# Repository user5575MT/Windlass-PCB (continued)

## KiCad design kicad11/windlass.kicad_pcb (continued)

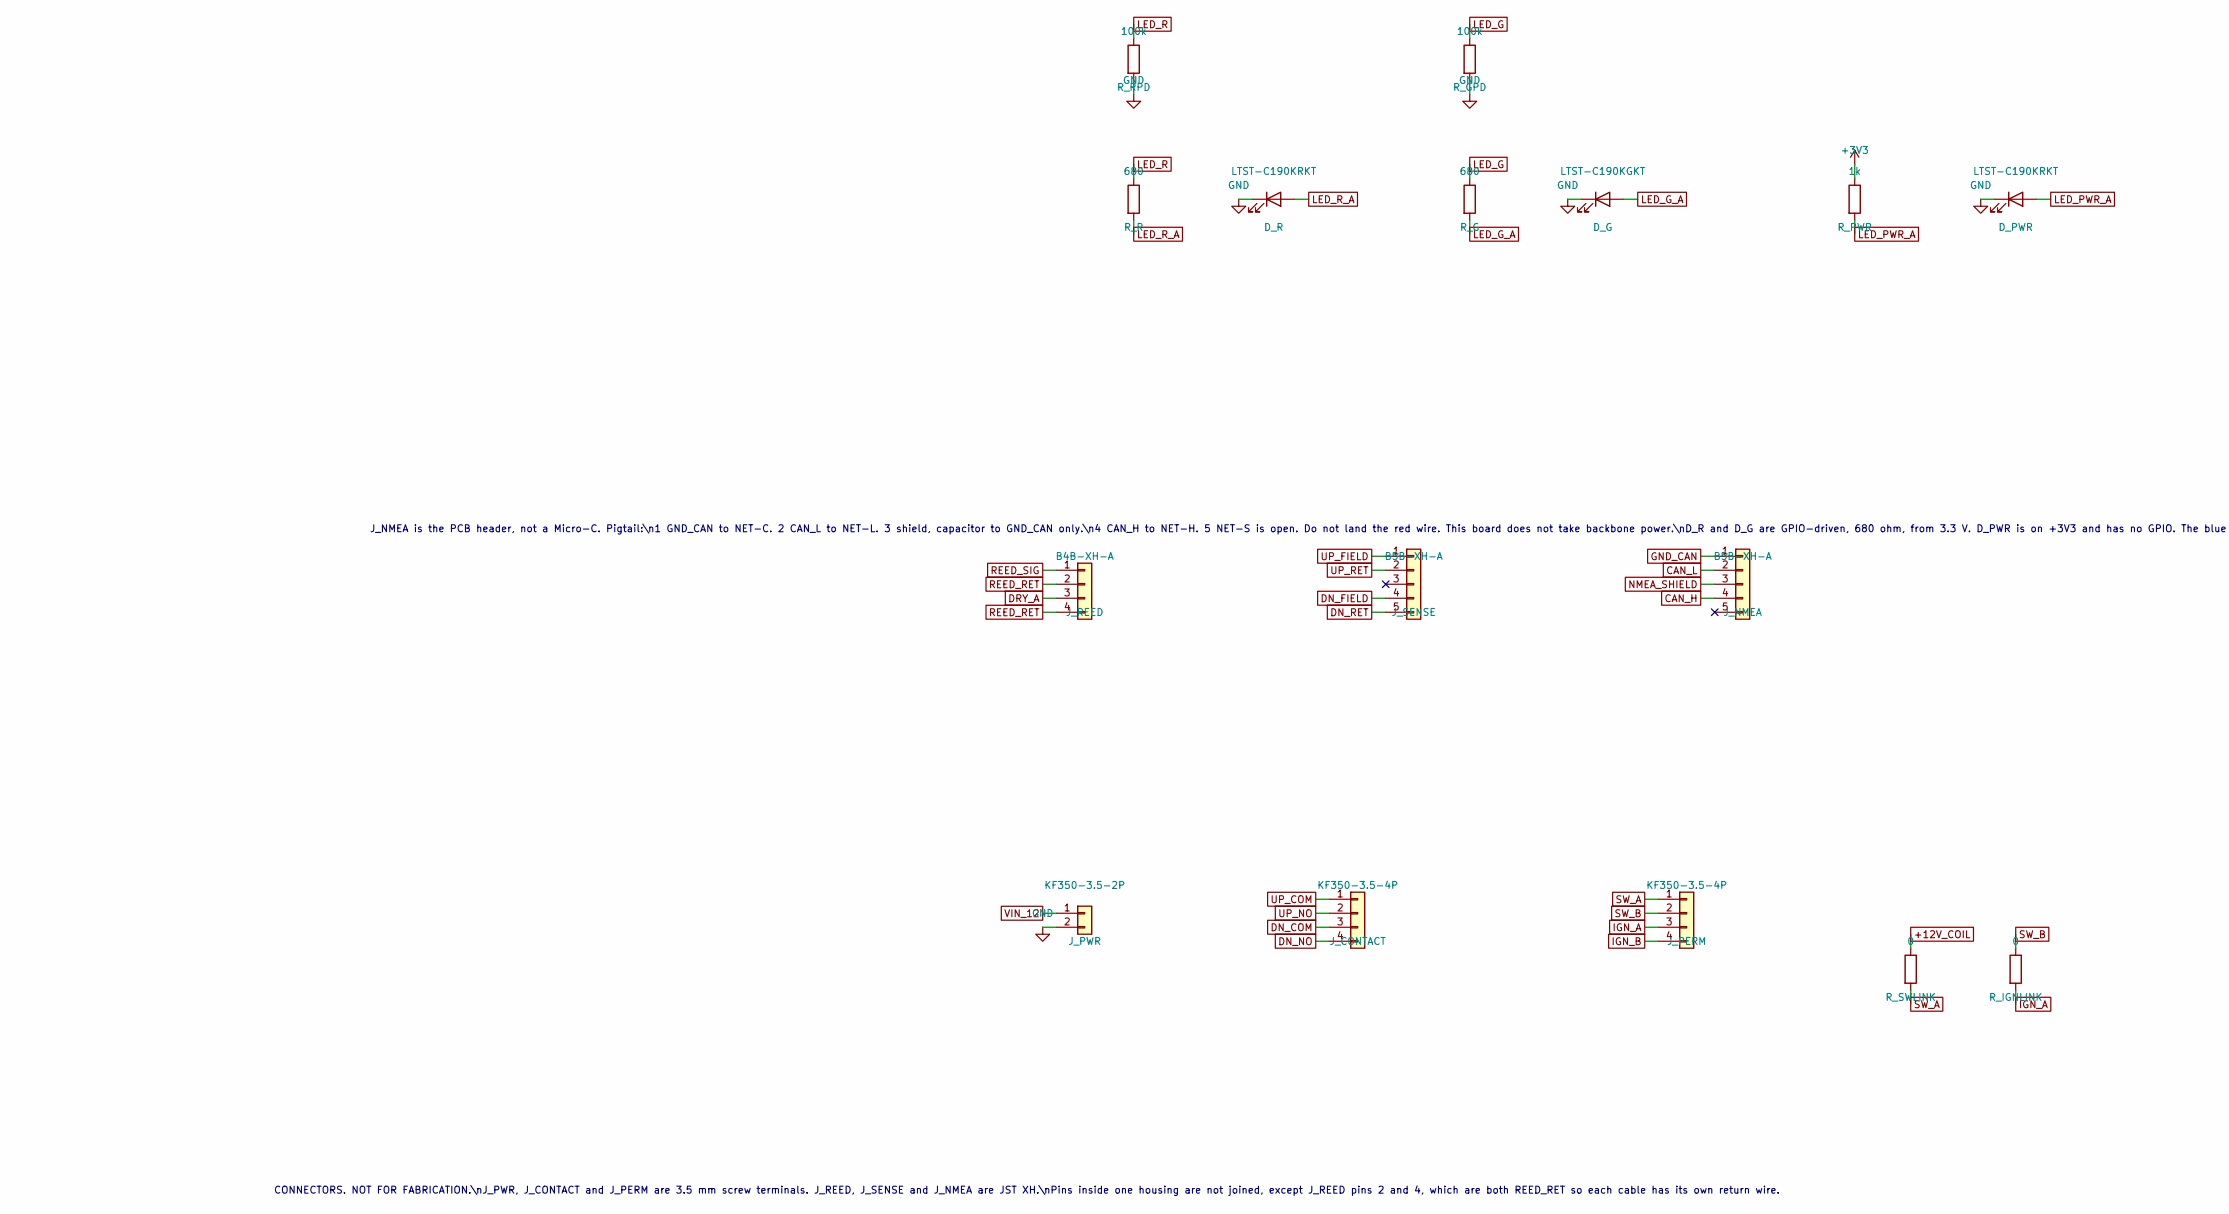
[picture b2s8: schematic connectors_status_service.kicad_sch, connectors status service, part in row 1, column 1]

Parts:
D_G: LTST-C190KGKT; LED_0603_1608Metric
D_PWR: LTST-C190KRKT; LED_0603_1608Metric
D_R: LTST-C190KRKT; LED_0603_1608Metric
J_CONTACT: KF350-3.5-4P; KF350-3.5-1x04
J_NMEA: B5B-XH-A; JST_XH_B5B-XH-A_1x05_P2.50mm_Vertical
J_PERM: KF350-3.5-4P; KF350-3.5-1x04
J_PWR: KF350-3.5-2P; KF350-3.5-1x02
J_REED: B4B-XH-A; JST_XH_B4B-XH-A_1x04_P2.50mm_Vertical
J_SENSE: B5B-XH-A; JST_XH_B5B-XH-A_1x05_P2.50mm_Vertical
R_G: 680; R_0402_1005Metric
R_GPD: 100k; R_0402_1005Metric
R_IGNLINK: 0; R_0402_1005Metric
R_PWR: 1k; R_0402_1005Metric
R_R: 680; R_0402_1005Metric
R_RPD: 100k; R_0402_1005Metric
R_SWLINK: 0; R_0402_1005Metric

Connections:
+3V3: R_PWR.1; also elsewhere on the board
+12V_COIL: R_SWLINK.1; also elsewhere on the board
CAN_H: J_NMEA.4; also elsewhere on the board
CAN_L: J_NMEA.2; also elsewhere on the board
DN_COM: J_CONTACT.3; also elsewhere on the board
DN_FIELD: J_SENSE.4; also elsewhere on the board
DN_NO: J_CONTACT.4; also elsewhere on the board
DN_RET: J_SENSE.5; also elsewhere on the board
DRY_A: J_REED.3; also elsewhere on the board
GND: D_G.1 (K), D_PWR.1 (K), D_R.1 (K), J_PWR.2, R_GPD.2, R_RPD.2; also elsewhere on the board
GND_CAN: J_NMEA.1; also elsewhere on the board
IGN_A: J_PERM.3, R_IGNLINK.2
IGN_B: J_PERM.4; also elsewhere on the board
LED_G: R_G.1, R_GPD.1; also elsewhere on the board
LED_G_A: D_G.2 (A), R_G.2
LED_PWR_A: D_PWR.2 (A), R_PWR.2
LED_R: R_R.1, R_RPD.1; also elsewhere on the board
LED_R_A: D_R.2 (A), R_R.2
NMEA_SHIELD: J_NMEA.3; also elsewhere on the board
REED_RET: J_REED.2, J_REED.4; also elsewhere on the board
REED_SIG: J_REED.1; also elsewhere on the board
SW_A: J_PERM.1, R_SWLINK.2
SW_B: J_PERM.2, R_IGNLINK.1
UP_COM: J_CONTACT.1; also elsewhere on the board
UP_FIELD: J_SENSE.1; also elsewhere on the board
UP_NO: J_CONTACT.2; also elsewhere on the board
UP_RET: J_SENSE.2; also elsewhere on the board
VIN_12: J_PWR.1; also elsewhere on the board

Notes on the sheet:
CONNECTORS. NOT FOR FABRICATION.\nJ_PWR, J_CONTACT and J_PERM are 3.5 mm screw terminals. J_REED, J_SENSE and J_NMEA are JST XH.\nPins inside one housing are not joined, except J_REED pins 2 and 4, which are both REED_RET so each cable has its own return wire.
J_NMEA is the PCB header, not a Micro-C. Pigtail:\n1 GND_CAN to NET-C. 2 CAN_L to NET-L. 3 shield, capacitor to GND_CAN only.\n4 CAN_H to NET-H. 5 NET-S is open. Do not land the red wire. This board does not take backbone power.\nD_R and D_G are GPIO-driven, 680 ohm, from 3.3 V. D_PWR is on +3V3 an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

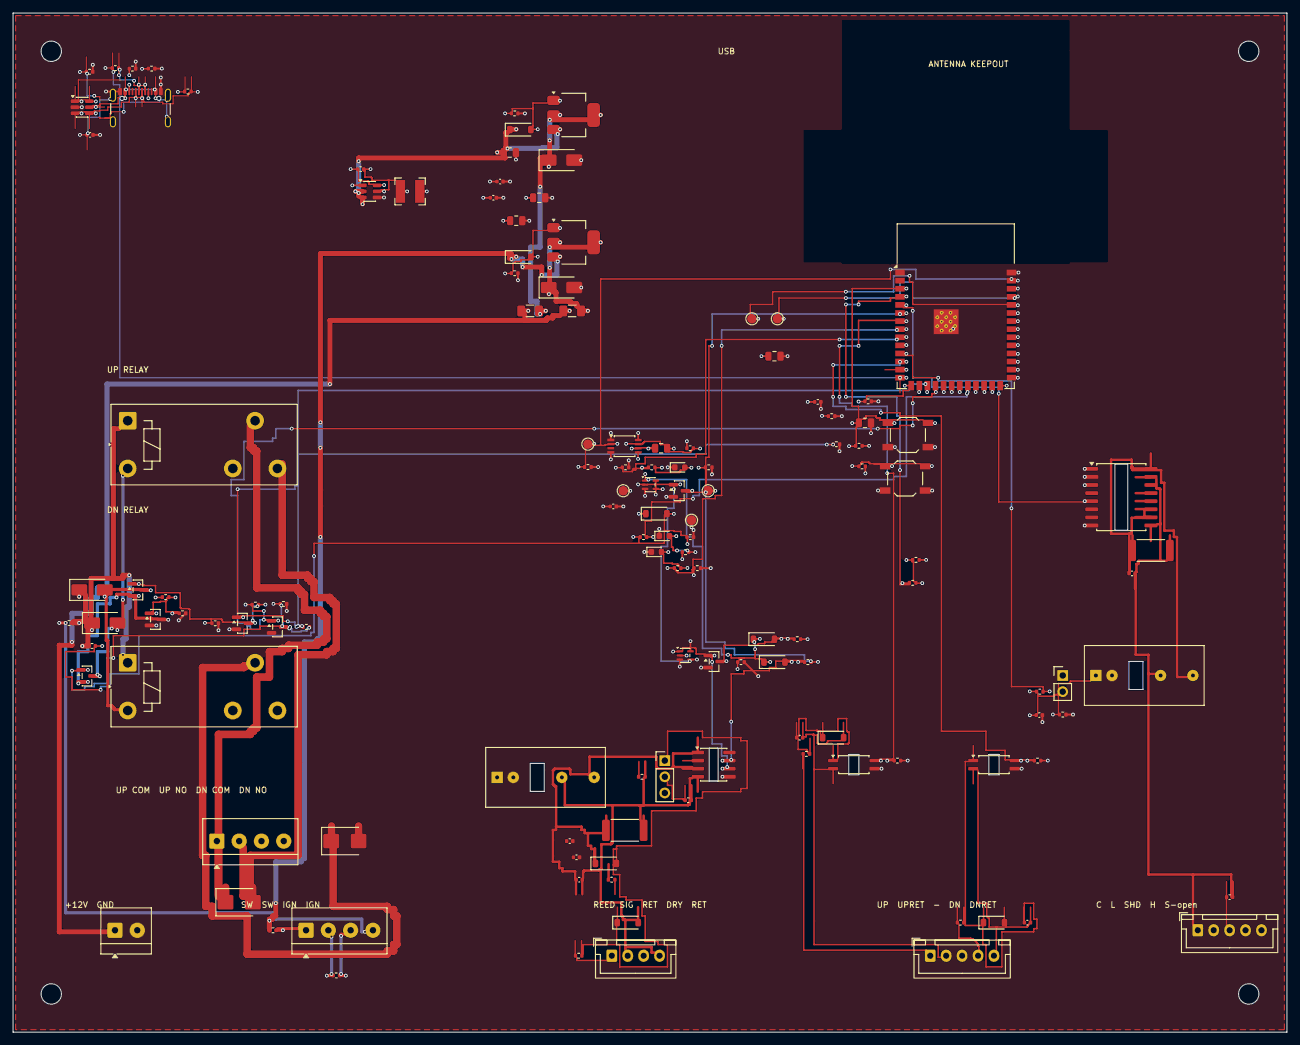
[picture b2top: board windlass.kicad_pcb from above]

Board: 4 copper layers, 200.0 x 160.0 mm, 134 parts (0 on the bottom side), 83 nets.

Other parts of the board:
H1, H2, H3, H4: M3; MountingHole_3.2mm_M3

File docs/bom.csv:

"Reference","Value","Footprint"
"C10","1uF","Capacitor_SMD:C_0805_2012Metric"
"C11","10uF","Capacitor_SMD:C_0805_2012Metric"
"C12","100nF","Capacitor_SMD:C_0402_1005Metric"
"C13","100nF","Capacitor_SMD:C_0402_1005Metric"
"C20","100nF","Capacitor_SMD:C_0402_1005Metric"
"C21","100nF","Capacitor_SMD:C_0402_1005Metric"
"C22","1nF","Capacitor_SMD:C_0402_1005Metric"
"C24","100nF","Capacitor_SMD:C_0402_1005Metric"
"C30","100nF","Capacitor_SMD:C_0402_1005Metric"
"C30A?","22uF","Capacitor_SMD:C_0805_2012Metric"
"C30B?","100nF","Capacitor_SMD:C_0402_1005Metric"
"C30C?","22uF","Capacitor_SMD:C_0805_2012Metric"
"C30I?","10uF","Capacitor_SMD:C_0805_2012Metric"
"C40","100nF","Capacitor_SMD:C_0402_1005Metric"
"C40A?","22uF","Capacitor_SMD:C_0805_2012Metric"
"C40B?","100nF","Capacitor_SMD:C_0402_1005Metric"
"C40C?","22uF","Capacitor_SMD:C_0805_2012Metric"
"C40I?","10uF","Capacitor_SMD:C_0805_2012Metric"
"C50","3.3uF","Capacitor_SMD:C_0805_2012Metric"
"C51","100nF","Capacitor_SMD:C_0402_1005Metric"
"C90","100nF","Capacitor_SMD:C_0402_1005Metric"
"C91","100nF","Capacitor_SMD:C_0402_1005Metric"
"C92","100nF","Capacitor_SMD:C_0402_1005Metric"
"C93","100nF","Capacitor_SMD:C_0402_1005Metric"
"D20","BAT54W","Diode_SMD:D_SOD-123"
"D21","BAT54W","Diode_SMD:D_SOD-123"
"D30","1N4148W_ANTIPARALLEL","Diode_SMD:D_SOD-123"
"D40","1N4148W_ANTIPARALLEL","Diode_SMD:D_SOD-123"
"D60","SS14","Diode_SMD:D_SMA"
"D70","SS14","Diode_SMD:D_SMA"
"D80","SCHOTTKY_CLAMP","Diode_SMD:D_SOD-123"
"D_B?","LTST-C190TBKT","LED_SMD:LED_0603_1608Metric"
"D_G?","LTST-C190KGKT","LED_SMD:LED_0603_1608Metric"
"D_R?","LTST-C190KRKT","LED_SMD:LED_0603_1608Metric"
"D_TVS_COIL?","SMAJ18A","Diode_SMD:D_SMA"
"D_TVS_MCU?","SMAJ18A","Diode_SMD:D_SMA"
"D_Z_COIL?","BZT52C12","Diode_SMD:D_SOD-123"
"D_Z_MCU?","BZT52C12","Diode_SMD:D_SOD-123"
"F_5V?","2A_antisurge","Fuse:Fuse_1206_3216Metric"
"F_COIL?","1A_0466001","Fuse:Fuse_1206_3216Metric"
"F_MCU?","2A_0466002","Fuse:Fuse_1206_3216Metric"
"JP1","Jumper_2_Open","Connector_PinHeader_2.54mm:PinHeader_1x02_P2.54mm_Vertical"
"JP_REED?","HDR_1x03_2.54","Connector_PinHeader_2.54mm:PinHeader_1x03_P2.54mm_Vertical"
"J_CONTACT?","KF350-3.5-4P","windlass:KF350-3.5-1x04"
"J_NMEA?","B5B-XH-A(LF)(SN)","Connector_JST:JST_XH_B5B-XH-A_1x05_P2.50mm_Vertical"
"J_PERM?","KF350-3.5-4P","windlass:KF350-3.5-1x04"
"J_PWR?","KF350-3.5-2P","windlass:KF350-3.5-1x02"
"J_REED?","B4B-XH-A(LF)(SN)","Connector_JST:JST_XH_B4B-XH-A_1x04_P2.50mm_Vertical"
"J_SENSE?","B5B-XH-A(LF)(SN)","Connector_JST:JST_XH_B5B-XH-A_1x05_P2.50mm_Vertical"
"J_USB?","TYPE-C-31-M-12","Connector_USB:USB_C_Receptacle_HRO_TYPE-C-31-M-12"
"K_DN?","40.31.7.012.0000","Relay_THT:Relay_SPDT_Finder_40.31"
"K_UP?","40.31.7.012.0000","Relay_THT:Relay_SPDT_Finder_40.31"
"L20","3.9uH","Inductor_SMD:L_Bourns-SRN4018"
"L21","4.7uH","Inductor_SMD:L_Bourns-SRN4018"
"Q90","2N7002","Package_TO_SOT_SMD:SOT-23"
"Q91","DMP3099L","Package_TO_SOT_SMD:SOT-23"
"Q_CLAMP_DN?","2N7002","Package_TO_SOT_SMD:SOT-23"
"Q_CLAMP_UP?","2N7002","Package_TO_SOT_SMD:SOT-23"
"Q_COIL?","DMP6023LE-13","Package_TO_SOT_SMD:SOT-223-3_TabPin2"
"Q_DN?","NX6008NBK","Package_TO_SOT_SMD:SOT-23"
"Q_LED?","2N7002BK,215","Package_TO_SOT_SMD:SOT-23"
"Q_MCU?","DMP6023LE-13","Package_TO_SOT_SMD:SOT-223-3_TabPin2"
"Q_SERIES?","NX6008NBK","Package_TO_SOT_SMD:SOT-23"
"Q_UP?","NX6008NBK","Package_TO_SOT_SMD:SOT-23"
"R10","10k","Resistor_SMD:R_0402_1005Metric"
"R11","10k","Resistor_SMD:R_0402_1005Metric"
"R12","10k","Resistor_SMD:R_0402_1005Metric"
"R13","100k","Resistor_SMD:R_0402_1005Metric"
"R14","100k","Resistor_SMD:R_0402_1005Metric"
"R15","5.1k","Resistor_SMD:R_0402_1005Metric"
"R16","5.1k","Resistor_SMD:R_0402_1005Metric"
"R17","22","Resistor_SMD:R_0402_1005Metric"
"R18","22","Resistor_SMD:R_0402_1005Metric"
"R19","1M","Resistor_SMD:R_0402_1005Metric"
"R20","10k","Resistor_SMD:R_0402_1005Metric"
"R22","4.7k","Resistor_SMD:R_0402_1005Metric"
"R23","47k","Resistor_SMD:R_0402_1005Metric"
"R24","51_0.5W","Resistor_SMD:R_2512_6332Metric"
"R30","R_IN_OPEN","Resistor_SMD:R_0402_1005Metric"
"R30P?","10k","Resistor_SMD:R_0402_1005Metric"
"R40","R_IN_OPEN","Resistor_SMD:R_0402_1005Metric"
"R40P?","10k","Resistor_SMD:R_0402_1005Metric"
"R50","100","Resistor_SMD:R_0402_1005Metric"
"R51","100k","Resistor_SMD:R_0402_1005Metric"
"R52","100k","Resistor_SMD:R_0402_1005Metric"
"R53","100k","Resistor_SMD:R_0402_1005Metric"
"R60","10k","Resistor_SMD:R_0402_1005Metric"
"R61","100k","Resistor_SMD:R_0402_1005Metric"
"R70","10k","Resistor_SMD:R_0402_1005Metric"
"R71","100k","Resistor_SMD:R_0402_1005Metric"
"R80","100k","Resistor_SMD:R_0402_1005Metric"
"R81","100k","Resistor_SMD:R_0402_1005Metric"
"R82","1k","Resistor_SMD:R_0402_1005Metric"
"R90","100k","Resistor_SMD:R_0402_1005Metric"
"R91","100k","Resistor_SMD:R_0402_1005Metric"
"R92","10k","Resistor_SMD:R_0402_1005Metric"
"R93","33","Resistor_SMD:R_0402_1005Metric"
"R94","120_0.5W","Resistor_SMD:R_2512_6332Metric"
"R_B?","1k","Resistor_SMD:R_0402_1005Metric"
"R_BPD?","100k","Resistor_SMD:R_0402_1005Metric"
"R_COILFEED?","0","Resistor_SMD:R_0402_1005Metric"
"R_COIL_G?","100k","Resistor_SMD:R_0402_1005Metric"
"R_G?","680","Resistor_SMD:R_0402_1005Metric"
"R_GPD?","100k","Resistor_SMD:R_0402_1005Metric"
"R_IGNLINK?","0","Resistor_SMD:R_0402_1005Metric"
"R_MCU_G?","100k","Resistor_SMD:R_0402_1005Metric"
"R_R?","680","Resistor_SMD:R_0402_1005Metric"
"R_RPD?","100k","Resistor_SMD:R_0402_1005Metric"
"R_SWLINK?","0","Resistor_SMD:R_0402_1005Metric"
"SH_REED?","SHUNT_2.54",""
"SW_BOOT?","TL3342F160QG","Button_Switch_SMD:SW_SPST_TL3342"
"SW_RST?","TL3342F160QG","Button_Switch_SMD:SW_SPST_TL3342"
"TP_RX?","TESTPAD","TestPoint:TestPoint_Pad_D1.5mm"
"TP_TX?","TESTPAD","TestPoint:TestPoint_Pad_D1.5mm"
"TP_VBUS?","TESTPAD","TestPoint:TestPoint_Pad_D1.5mm"
"TP_WDI?","TESTPAD","TestPoint:TestPoint_Pad_D1.5mm"
"U3","ESP32-S3-WROOM-1-N16","RF_Module:ESP32-S3-WROOM-1"
"U4","MEJ2S0503SC","windlass:Murata_MEJ2SxxxxSC"
"U5","ISO7721DR","Package_SO:SOIC-8_3.9x4.9mm_P1.27mm"
"U6","TLP291(GB-TP,SE","Package_SO:SOIC-4_4.55x2.6mm_P1.27mm"
"U7","TLP291(GB-TP,SE","Package_SO:SOIC-4_4.55x2.6mm_P1.27mm"
"U8","74LVC1G86GW,125","Package_TO_SOT_SMD:SOT-353_SC-70-5"
"U9","MEJ2S0505SC","windlass:Murata_MEJ2SxxxxSC"
"U10","ISO1042BDWR","Package_SO:SOIC-16W_7.5x10.3mm_P1.27mm"
"U11","74LVC1G123DP,125","Package_SO:TSSOP-8_3x3mm_P0.65mm"
"U12","74LVC1G08GW,125","Package_TO_SOT_SMD:SOT-353_SC-70-5"
"U20","AP63203WU","Package_TO_SOT_SMD:TSOT-23-6"
"U21","AP63205WU","Package_TO_SOT_SMD:TSOT-23-6"
"U_ESD?","USBLC6-2SC6","Package_TO_SOT_SMD:SOT-23-6"

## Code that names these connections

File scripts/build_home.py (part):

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    s.flag(120, 560, "CAN_VIN")

    # --- 12 V input, two branches ---
    bs.multi_pin(s, "Connector_Generic:Conn_01x02", "J_PWR", "KF350-3.5-2P", *cell(0, 0), ["VIN_12", "GND"], FP["kf2"])
    bs.two_pin(s, "Device:Fuse", "F_MCU", "0217002.HXP", *cell(0, 1), "VIN_12", "VIN_MCU", FP["fuse"])
    bs.two_pin(s, "Device:D", "D_TVS_MCU", "P6KE18A", *cell(0, 2), "VIN_MCU", "GND", FP["d"])
    q = s.place("Transistor_FET:IRF9540N", "Q_MCU", "IRF9540NPBF", *cell(1, 0), FP["fet"])
    bs.connect_named(s, q, {"D": "VIN_MCU", "S": "+12V_MCU", "G": "QMCU_G"})
    bs.two_pin(s, "Device:R", "R_MCU_G", "100k", *cell(1, 1), "QMCU_G", "GND", FP["r"])
    bs.two_pin(s, "Device:D", "D_Z_MCU", "BZX55C12", *cell(1, 2), "+12V_MCU", "QMCU_G", FP["dz"])
    bs.two_pin(s, "Device:C_Polarized", "C_IN", "10uF_50V", *cell(1, 3), "+12V_MCU", "GND", FP["cp10"])

    bs.two_pin(s, "Device:Fuse", "F_COIL", "0235.250HXP", *cell(0, 3), "VIN_12", "VIN_COIL", FP["fuse"])
    bs.two_pin(s, "Device:D", "D_TVS_COIL", "P6KE18A", *cell(0, 4), "VIN_COIL", "GND", FP["d"])
    q = s.place("Transistor_FET:IRF9540N", "Q_COIL", "IRF9540NPBF", *cell(1, 4), FP["fet"])
    bs.connect_named(s, q, {"D": "VIN_COIL", "S": "+12V_COIL", "G": "QCOIL_G"})
    bs.two_pin(s, "Device:R", "R_COIL_G", "100k", *cell(2, 0), "QCOIL_G", "GND", FP["r"])
    bs.two_pin(s, "Device:D", "D_Z_COIL", "BZX55C12", *cell(2, 1), "+12V_COIL", "QCOIL_G", FP["dz"])

    u = s.place("Converter_DCDC:OKI-78SR-5_1.5-W36H-C", "U20", "OKI-78SR-5/1.5-W36H-C", *cell(2, 2), FP["oki"])
    bs.connect_named(s, u, {"IN": "+12V_MCU", "GND": "GND", "OUT": "+5V"})
    bs.two_pin(s, "Device:C_Polarized", "C_5V", "10uF_25V", *cell(2, 3), "+5V", "GND", FP["cp"])
    bs.two_pin(s, "Device:C", "C_5VHF", "100nF", *cell(2, 4), "+5V", "GND", FP["c"])
    # Anode is pin 2, cathode is pin 1. Current flows from +5V into the DevKit only.
    bs.two_pin(s, "Diode:1N5817", "D_DEV", "1N5817", *cell(3, 0), "DEV_5V", "+5V", FP["d"])
    bs.two_pin(s, "Device:C_Polarized", "C_DEV", "10uF_25V", *cell(3, 1), "DEV_5V", "GND", FP["cp"])

    # --- DevKit sockets. Pin 1 of both headers is the USB end, opposite the antenna. ---
    j1 = {
        "1": "+3V3", "2": "+3V3", "4": "GPIO4", "5": "GPIO5", "6": "GPIO6",
        "7": "GPIO7", "8": "GPIO15", "9": "GPIO16", "11": "GPIO18", "12": "GPIO8",
        "15": "GPIO9", "16": "GPIO10", "20": "GPIO14", "21": "DEV_5V", "22": "GND",
    }
    j3 = {"1": "GND", "4": "GPIO1", "21": "GND", "22": "GND"}
    bs.connect_named(
        s,
        s.place("Connector_Generic:Conn_01x22", "J1", "DevKitC_J1", *cell(0, 6), FP["sock"]),
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        s,
        u,
        {
            "1A": "GPIO1",
            "1Y": "HB_N",
            "2A": "EDGE",
            "2Y": "DISCH",
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            "GND": "GND",
        },
    )
    bs.two_pin(s, "Device:R", "R_HB", "100k", *cell(4, 2), "GPIO1", "GND", FP["r"])
    bs.two_pin(s, "Device:R", "R_EDGE", "330", *cell(4, 3), "HB_N", "EDGE_R", FP["r"])
    bs.two_pin(s, "Device:C", "C_EDGE", "220nF", *cell(5, 0), "EDGE_R", "EDGE", FP["c"])
    bs.two_pin(s, "Device:R", "R_EDGE_PU", "10k", *cell(5, 1), "EDGE", "+5V", FP["r"])
    bs.two_pin(s, "Device:R", "R_BASE", "1k", *cell(5, 2), "DISCH", "DISCH_B", FP["r"])
    q = s.place("Transistor_BJT:BC547", "Q_DIS", "BC547B", *cell(5, 3), FP["q"])
    bs.connect_named(s, q, {"B": "DISCH_B", "C": "TIME", "E": "GND"})
    bs.two_pin(s, "Device:R", "R_TIME", "470k", *cell(5, 4), "+5V", "TIME", FP["r"])
    bs.two_pin(s, "Device:C", "C_TIME", "2.2uF", *cell(6, 0), "TIME", "GND", FP["cfilm"])
    bs.two_pin(s, "Device:C", "C_U12", "100nF", *cell(6, 1), "+5V", "GND", FP["c"])
    bs.two_pin(s, "Device:R", "R50", "470", *cell(6, 2), "WDI_Q", "WDI_GATE", FP["r"])
    bs.two_pin(s, "Device:R", "R_SER_PD", "100k", *cell(6, 3), "WDI_GATE", "GND", FP["r"])

    # --- Request buffers and coil FETs ---
    u = s.place("windlass:CD74HCT125E", "U15", "CD74HCT125E", *cell(7, 0), FP["dip14"])
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        u,
        {
            "1OE": "GND",
            "1A": "GPIO9",
            "1Y": "UP_DRV",
            "2OE": "GND",
            "2A": "GPIO10",
            "2Y": "DN_DRV",
            "3OE": "+5V",
            "3A": "GND",
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        },
    )
    bs.two_pin(s, "Device:C", "C_U15", "100nF", *cell(7, 2), "+5V", "GND", FP["c"])
    bs.two_pin(s, "Device:R", "R13", "100k", *cell(7, 3), "GPIO9", "GND", FP["r"])
    bs.two_pin(s, "Device:R", "R14", "100k", *cell(7, 4), "GPIO10", "GND", FP["r"])
    bs.two_pin(s, "Device:R", "R60", "470", *cell(8, 0), "UP_DRV", "UP_GATE", FP["r"])
    bs.two_pin(s, "Device:R", "R61", "100k", *cell(8, 1), "UP_GATE", "GND", FP["r"])
    bs.two_pin(s, "Device:R", "R70", "470", *cell(8, 2), "DN_DRV", "DN_GATE", FP["r"])
    bs.two_pin(s, "Device:R", "R71", "100k", *cell(8, 3), "DN_GATE", "GND", FP["r"])
    # Opposite request clamps the other gate. Both high holds both gates off.
    bs.two_pin(s, "Device:R", "R_CL_UP", "4.7k", *cell(8, 4), "DN_DRV", "CLUP_B", FP["r"])
    bs.two_pin(s, "Device:R", "R_CL_DN", "4.7k", *cell(9, 0), "UP_DRV", "CLDN_B", FP["r"])
    q = s.place("Transistor_BJT:BC547", "Q_CL_UP", "BC547B", *cell(9, 1), FP["q"])
    bs.connect_named(s, q, {"B": "CLUP_B", "C": "UP_GATE", "E": "GND"})
    q = s.place("Transistor_BJT:BC547", "Q_CL_DN", "BC547B", *cell(9, 2), FP["q"])
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        bs.connect_named(s, q, {"G": gate, "D": drain, "S": "SERIES_DRAIN"})
    q = s.place("Transistor_FET:IRLZ44N", "Q_SERIES", "IRLZ44NPBF", *cell(10, 0), FP["fet"])
    bs.connect_named(s, q, {"G": "WDI_GATE", "D": "SERIES_DRAIN", "S": "GND"})
    bs.two_pin(s, "Diode:1N5819", "D60", "1N5819", *cell(10, 1), "COIL_12", "UP_LOW", FP["d"])
    bs.two_pin(s, "Diode:1N5819", "D70", "1N5819", *cell(10, 2), "COIL_12", "DN_LOW", FP["d"])

    k = s.place("Relay:Relay_SPDT", "K_UP", "40.31.7.012.0000", *cell(10, 3), FP["relay"])
    bs.connect_named(s, k, {"A1": "COIL_12", "A2": "UP_LOW", "11": "UP_COM", "14": "UP_NO"})
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        s, "Connector_Generic:Conn_01x04", "J_CONTACT", "KF350-3.5-4P", *cell(11, 1),
        ["UP_COM", "UP_NO", "DN_COM", "DN_NO"], FP["kf4"],
    )
    bs.two_pin(s, "Device:R", "R80", "100k", *cell(11, 2), "COIL_12", "COIL_DIV", FP["r"])
    bs.two_pin(s, "Device:R", "R81", "100k", *cell(11, 3), "COIL_DIV", "GND", FP["r"])
    bs.two_pin(s, "Diode:BAT46", "D80", "BAT46", *cell(11, 4), "+3V3", "COIL_DIV", FP["dz"])
    bs.two_pin(s, "Device:R", "R82", "1k", *cell(12, 0), "COIL_DIV", "GPIO14", FP["r"])

    # LEDs, sourced by the GPIO. High lights the lamp.
    bs.two_pin(s, "Device:R", "R_R", "680", *cell(12, 1), "GPIO15", "LED_R", FP["r"])
    bs.two_pin(s, "Device:LED", "D_R", "RED", *cell(12, 2), "GND", "LED_R", FP["led"])
    bs.two_pin(s, "Device:R", "R_G", "680", *cell(12, 3), "GPIO16", "LED_G", FP["r"])
    bs.two_pin(s, "Device:LED", "D_G", "GREEN", *cell(12, 4), "GND", "LED_G", FP["led"])

    # --- Reed, isolated side ---
    u = s.place("windlass:MEJ2S", "U4", "MEJ2S0503SC", *cell(0, 8), FP["mej"])
    bs.connect_named(s, u, {"+Vin": "+5V", "-Vin": "GND", "+Vout": "REED_3V3", "-Vout": "REED_RET"})
    bs.two_pin(s, "Device:R", "R24", "51", *cell(1, 8), "REED_3V3", "REED_RET", FP["r1w"])
    bs.two_pin(s, "Device:C_Polarized", "C_REED", "10uF_16V", *cell(2, 8), "REED_3V3", "REED_RET", FP["cp"])
    bs.multi_pin(
        s, "Connector_Generic:Conn_01x04", "J_REED", "B4B-XH-A", *cell(3, 8),
        ["REED_SIG", "REED_RET", "DRY_A", "REED_RET"], FP["xh4"],
    )
    jp = s.place("Jumper:Jumper_3_Bridged12", "JP_REED", "1x03", *cell(4, 8), FP["jp3"])
    bs.connect_named(s, jp, {"A": "LOFRANS_NODE", "C": "REED_ISO", "B": "DRY_A"})
    bs.two_pin(s, "Device:R", "R20", "10k", *cell(5, 8), "REED_SIG", "LOFRANS_NODE", FP["r"])
    bs.two_pin(s, "Device:R", "R23", "47k", *cell(6, 8), "REED_ISO", "REED_RET", FP["r"])
    bs.two_pin(s, "Device:R", "R22", "4.7k", *cell(7, 8), "REED_3V3", "DRY_A", FP["r"])
    bs.two_pin(s, "Diode:BAT46", "D20", "BAT46", *cell(8, 8), "REED_3V3", "LOFRANS_NODE", FP["dz"])
    bs.two_pin(s, "Diode:BAT46", "D21", "BAT46", *cell(9, 8), "LOFRANS_NODE", "REED_RET", FP["dz"])
    q = s.place("Transistor_BJT:BC557", "Q_REED", "BC557B", *cell(10, 8), FP["q"])
    bs.connect_named(s, q, {"E": "REED_3V3", "B": "REED_B", "C": "REED_C"})
    bs.two_pin(s, "Device:R", "R_REED_B", "47k", *cell(11, 8), "REED_ISO", "REED_B", FP["r"])
    bs.two_pin(s, "Device:R", "R_REED_C", "1k", *cell(12, 8), "REED_C", "RD_A", FP["r"])
    u = s.place("Isolator:PC817", "U_RD", "PC817", *cell(13, 6), FP["dip4"])
    bs.connect_named(s, u, {"1": "RD_A", "2": "REED_RET", "3": "GND", "4": "REED_DATA"})
    bs.two_pin(s, "Device:R", "R_DATA", "10k", *cell(13, 7), "+3V3", "REED_DATA", FP["r"])
    bs.two_pin(s, "Device:R", "R_PG", "1k", *cell(13, 8), "REED_3V3", "PG_A", FP["r"])
    u = s.place("Isolator:PC817", "U_PG", "PC817", *cell(14, 6), FP["dip4"])
    bs.connect_named(s, u, {"1": "PG_A", "2": "REED_RET", "3": "GND", "4": "PG_N"})
    bs.two_pin(s, "Device:R", "R_PGPU", "10k", *cell(14, 7), "+3V3", "PG_N", FP["r"])

    # Blanker. BLOCKED sets while the field rail is down and clears only on a real low.
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
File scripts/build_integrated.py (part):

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        "Contactor-coil current does not enter this 12 V input. It flows through the relay contacts from the boat's existing control feed.",
    )
    s.flag(25, 210, "VIN_12")
    two_pin(s, "Device:Fuse", "F_MCU", "2A_0466002", 55, 200, "VIN_12", "VIN_MCU", "Fuse:Fuse_1206_3216Metric")
    two_pin(s, "Diode:SMAJ18A", "D_TVS_MCU", "SMAJ18A", 90, 200, "VIN_MCU", "GND", "Diode_SMD:D_SMA")
    q = s.place(
        "windlass:DMP6023LE",
        "Q_MCU",
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        "Package_TO_SOT_SMD:SOT-223-3_TabPin2",
    )
    connect_named(s, q, {"D": "VIN_MCU", "S": "+12V_MCU", "G": "QMCU_G"})
    two_pin(s, "Device:R", "R_MCU_G", "100k", 140, 175, "QMCU_G", "GND")
    two_pin(s, "windlass:DIODE_OPEN", "D_Z_MCU", "BZT52C12", 170, 200, "+12V_MCU", "QMCU_G", "Diode_SMD:D_SOD-123")
    s.flag(175, 215, "+12V_MCU")
    _buck(s, 40, 120)
    s.flag(40, 70, "+3V3")
    two_pin(s, "Device:Fuse", "F_COIL", "1A_0466001", 40, 40, "VIN_12", "VIN_COIL", "Fuse:Fuse_1206_3216Metric")
    two_pin(s, "Diode:SMAJ18A", "D_TVS_COIL", "SMAJ18A", 80, 40, "VIN_COIL", "GND", "Diode_SMD:D_SMA")
    qc = s.place(
        "windlass:DMP6023LE",
        "Q_COIL",
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        "Package_TO_SOT_SMD:SOT-223-3_TabPin2",
    )
    connect_named(s, qc, {"D": "VIN_COIL", "S": "+12V_COIL", "G": "QCOIL_G"})
    two_pin(s, "Device:R", "R_COIL_G", "100k", 130, 18, "QCOIL_G", "GND")
    two_pin(s, "windlass:DIODE_OPEN", "D_Z_COIL", "BZT52C12", 165, 40, "+12V_COIL", "QCOIL_G", "Diode_SMD:D_SOD-123")
    s.flag(175, 55, "+12V_COIL")
    s.flag(20, 20, "GND")
    s.note(
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        "Package_TO_SOT_SMD:TSOT-23-6",
    )
    connect_named(s, u, {"IN": "+12V_MCU", "EN": "+12V_MCU", "GND": "GND", "SW": "SW_3V3", "BST": "BST_3V3", "FB": "+3V3"})
    two_pin(s, "Device:L", "L20", "3.9uH", x + 40, y + 10, "SW_3V3", "+3V3", "Inductor_SMD:L_Bourns-SRN4018")
    two_pin(s, "Device:C", "C30B", "100nF", x + 20, y - 20, "BST_3V3", "SW_3V3")
    two_pin(s, "Device:C", "C30I", "10uF", x - 20, y - 20, "+12V_MCU", "GND", "Capacitor_SMD:C_0805_2012Metric")
    two_pin(s, "Device:C", "C30A", "22uF", x + 60, y - 16, "+3V3", "GND", "Capacitor_SMD:C_0805_2012Metric")
    two_pin(s, "Device:C", "C30C", "22uF", x + 80, y - 16, "+3V3", "GND", "Capacitor_SMD:C_0805_2012Metric")
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    s.note(
        20,
        270,
        "ESP32-S3-WROOM-1-N16. NOT FOR FABRICATION. Prototype firmware is not modified and does not edge GPIO1.\\n"
        "EN: 10k to +3V3 and 1 uF to GND. GPIO0: 10k pull-up and a boot button. GPIO3: 10k to GND.\\n"
        "GPIO45 and GPIO46 stay open. Do not pull GPIO45 high. USB VBUS is not connected to +3V3.",
    )
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            "IO3": "IO3_NET",
            "IO4": "TWAI_TX",
            "IO5": "TWAI_RX",
            "IO6": "REED_GPIO",
            "IO7": "UP_SENSE",
            "IO8": "DN_SENSE",
            "IO9": "UP_REQ",
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            "RXD0": "UART_RX",
        },
    )
    two_pin(s, "Device:R", "R10", "10k", 40, 220, "EN_NET", "+3V3")
    two_pin(s, "Device:C", "C10", "1uF", 40, 200, "EN_NET", "GND")
    sw = s.place("Switch:SW_Push", "SW_RST", "TL3342F160QG", 70, 180, "Button_Switch_SMD:SW_SPST_TL3342")
    connect_named(s, sw, {"1": "EN_NET", "2": "GND"})
    two_pin(s, "Device:R", "R11", "10k", 40, 150, "IO0_NET", "+3V3")
    swb = s.place("Switch:SW_Push", "SW_BOOT", "TL3342F160QG", 70, 140, "Button_Switch_SMD:SW_SPST_TL3342")
    connect_named(s, swb, {"1": "IO0_NET", "2": "GND"})
    two_pin(s, "Device:R", "R12", "10k", 40, 110, "IO3_NET", "GND")
    two_pin(s, "Device:C", "C11", "10uF", 100, 220, "+3V3", "GND", "Capacitor_SMD:C_0805_2012Metric")
    two_pin(s, "Device:C", "C12", "100nF", 120, 220, "+3V3", "GND")
    two_pin(s, "Device:R", "R13", "100k", 100, 180, "UP_REQ", "GND")
    two_pin(s, "Device:R", "R14", "100k", 120, 180, "DN_REQ", "GND")
    usb = s.place(
        "Connector:USB_C_Receptacle_USB2.0_16P",
        "J_USB",
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    )
    two_pin(s, "Device:R", "R15", "5.1k", 250, 120, "CC1", "GND")
    two_pin(s, "Device:R", "R16", "5.1k", 270, 120, "CC2", "GND")
    two_pin(s, "Device:R", "R17", "22", 250, 140, "USB_DP", "USB_DP_C")
    two_pin(s, "Device:R", "R18", "22", 270, 140, "USB_DN", "USB_DN_C")
    esd = s.place(
        "Power_Protection:USBLC6-2SC6",
        "U_ESD",
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        "Package_TO_SOT_SMD:SOT-23-6",
    )
    connect_named(s, esd, {"I/O1": "USB_DP_C", "I/O2": "USB_DN_C", "GND": "GND", "VBUS": "USB_VBUS"})
    two_pin(s, "Device:R", "R19", "1M", 330, 80, "USB_SHIELD", "GND")
    two_pin(s, "Device:C", "C13", "100nF", 350, 80, "USB_SHIELD", "GND")
    for ref, net, x in (
        ("TP_TX", "UART_TX", 40),
        ("TP_RX", "UART_RX", 55),
        ("TP_WDI", "WDI_FUTURE", 70),
        ("TP_3V3", "+3V3", 85),
        ("TP_GND", "GND", 100),
        ("TP_REED", "REED_GPIO", 115),
    ):
        tp = s.place("Connector_Generic:Conn_01x01", ref, "TP", x, 80, "TestPoint:TestPoint_Pad_D1.5mm")
        p = pin(tp, num="1")[0]
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        20,
        40,
        "J_USB is a GCT USB4105 top-mount receptacle. Every signal pad is on the board. The earlier mid-mount HRO part is not used.\\n"
        "CC resistors are 5.1k Rd. D+ and D- have 22 ohm series resistors, then USBLC6-2SC6. Its VBUS pin is USB_VBUS, not +3V3.\\n"
        "R13 and R14 hold the coil requests low while the GPIOs are high-Z, including reset.",
    )

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    dcdc = s.place("windlass:MEJ2S", "U4", "MEJ2S0303SC", 40, 210, "windlass:Murata_MEJ2SxxxxSC")
    connect_named(s, dcdc, {"1": "+3V3", "2": "GND", "7": "REED_3V3", "5": "REED_RET"})
    two_pin(s, "Device:C", "C24", "100nF", 40, 180, "+3V3", "GND")
    two_pin(s, "Device:C", "C20", "100nF", 80, 180, "REED_3V3", "REED_RET")
    two_pin(s, "Device:R", "R24", "51_0.5W", 100, 180, "REED_3V3", "REED_RET", "Resistor_SMD:R_2512_6332Metric")
    two_pin(s, "Device:R", "R20", "10k", 140, 230, "REED_SIG", "LOFRANS_NODE")
    two_pin(s, "Device:D_Schottky", "D20", "BAT54W", 170, 230, "REED_3V3", "LOFRANS_NODE", "Diode_SMD:D_SOD-123")
    two_pin(s, "Device:D_Schottky", "D21", "BAT54W", 170, 210, "LOFRANS_NODE", "REED_RET", "Diode_SMD:D_SOD-123")
    jp = s.place(
        "Jumper:Jumper_3_Open",
        "JP_REED",
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    shunt = s.place("Connector_Generic:Conn_01x02", "SH_REED", "SHUNT_2.54", 250, 230, on_board="no")
    for p in shunt:
        s.nc(p)
    two_pin(s, "Device:R", "R22", "4.7k", 220, 180, "REED_3V3", "DRY_A")
    two_pin(s, "Device:R", "R23", "47k", 250, 180, "REED_ISO", "REED_RET")
    two_pin(s, "Device:C", "C22", "1nF", 270, 180, "REED_ISO", "REED_RET")
    iso = s.place("Isolator:ISO7720D", "U5", "ISO7720FDR", 320, 210, "Package_SO:SOIC-8_3.9x4.9mm_P1.27mm")
    connect_named(
        s,
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        },
    )
    two_pin(s, "Device:C", "C21", "100nF", 360, 180, "+3V3", "GND")
    # Blanker. /S = PG. /R = REED_DATA OR NOT PG. Q high forces the GPIO low.
    nfet = s.place("Transistor_FET:2N7002", "Q_NPG", "2N7002BK", 40, 120, "Package_TO_SOT_SMD:SOT-23")
    connect_named(s, nfet, {"G": "PG", "D": "NOT_PG", "S": "GND"})
    two_pin(s, "Device:R", "R25", "10k", 70, 120, "NOT_PG", "+3V3")
    two_pin(s, "Device:D_Schottky", "D22", "BAT54W", 100, 130, "OR_R", "REED_DATA", "Diode_SMD:D_SOD-123")
    two_pin(s, "Device:D_Schottky", "D23", "BAT54W", 100, 110, "OR_R", "NOT_PG", "Diode_SMD:D_SOD-123")
    two_pin(s, "Device:R", "R26", "100k", 130, 110, "OR_R", "GND")
    n1 = s.place("74xGxx:74LVC1G00", "U13", "74LVC1G00GW", 180, 130, "Package_TO_SOT_SMD:SOT-353_SC-70-5")
    connect_named(s, n1, {"1": "PG", "2": "NQ", "GND": "GND", "4": "BLOCKED", "5": "+3V3"})
    n2 = s.place("74xGxx:74LVC1G00", "U14", "74LVC1G00GW", 230, 110, "Package_TO_SOT_SMD:SOT-353_SC-70-5")
    connect_named(s, n2, {"1": "OR_R", "2": "BLOCKED", "GND": "GND", "4": "NQ", "5": "+3V3"})
    two_pin(s, "Device:C", "C25", "100nF", 180, 90, "+3V3", "GND")
    two_pin(s, "Device:R", "R27", "10k", 280, 130, "REED_DATA", "REED_GPIO")
    qblk = s.place("Transistor_FET:2N7002", "Q_BLK", "2N7002BK", 310, 110, "Package_TO_SOT_SMD:SOT-23")
    connect_named(s, qblk, {"G": "BLOCKED", "D": "REED_GPIO", "S": "GND"})
    two_pin(s, "Device:R", "R28", "100k", 340, 110, "REED_GPIO", "GND")
    s.note(
        20,
        40,
        "Lofrans load is 3.3 V / 47k = 70 uA, and only while the shunt is on pins 1-2. The 4.7k pull-up is on DRY_A and cannot reach REED_SIG in that position.\\n"
        "R20 is 10k in series. D20 and D21 clamp LOFRANS_NODE to the field 3.3 V rail. The Lofrans wire is not connected to an ESP32 pin.\\n"
        "MEJ2S0303SC is 3.3 V to 3.3 V. R24 is 51 ohm, about 65 mA, just over 10 percent of the 606 mA rating, so the published load envelope applies.\\n"
        "Murata: hipot 5.2 kVDC for 1 s, continuous functional barrier 2.4 kVDC. Not a safety barrier. The LCSC YLPTEC listing is not this part.\\n"
        "Blanker: ISO7720F outputs go low when the field side is unpowered. Q_NPG makes NOT_PG. The diode-OR and the two NAND gates are an SR latch.\\n"
        "/S is PG, so a field-supply loss sets BLOCKED and Q_BLK holds REED_GPIO low. That is a falling edge, which the existing firmware does not count.\\n"
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
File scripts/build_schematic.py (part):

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        "AP2112K is removed. 3.3 V is an AP63203 buck straight from +12V_MCU, so the Wi-Fi current is not dropped across a 1.7 V linear regulator.",
    )
    s.flag(25, 210, "VIN_12")
    two_pin(s, "Device:Fuse", "F_MCU", "2A_0466002", 55, 200, "VIN_12", "VIN_MCU")
    # SMAJ18A extends SM6T: pin 1 is the cathode end of the symbol, pin 2 the anode.
    two_pin(s, "Diode:SMAJ18A", "D_TVS_MCU", "SMAJ18A", 90, 200, "VIN_MCU", "GND", "Diode_SMD:D_SMA")
    q = s.place("windlass:DMP6023LE", "Q_MCU", "DMP6023LE-13", 140, 200)
    connect_named(s, q, {"D": "VIN_MCU", "S": "+12V_MCU", "G": "QMCU_G"})
    two_pin(s, "Device:R", "R_MCU_G", "100k", 140, 175, "QMCU_G", "GND")
    two_pin(s, "windlass:DIODE_OPEN", "D_Z_MCU", "BZT52C12", 170, 200, "+12V_MCU", "QMCU_G")
    s.flag(175, 215, "+12V_MCU")
    _buck(s, 40, 130, "U20", "AP63203WU", "L20", "3.9uH", "SW_3V3", "BST_3V3", "+3V3", "C30")
    # FB and the output capacitors stay on the buck side of F_5V. The fuse is the Murata input fuse.
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    s.flag(40, 80, "+3V3")
    s.flag(330, 130, "+5V")
    # Coil branch sized for the Finder coil current. The Lofrans contact current is still unmeasured.
    two_pin(s, "Device:Fuse", "F_COIL", "1A_0466001", 40, 50, "VIN_12", "VIN_COIL")
    two_pin(s, "Diode:SMAJ18A", "D_TVS_COIL", "SMAJ18A", 80, 50, "VIN_COIL", "GND", "Diode_SMD:D_SMA")
    qc = s.place("windlass:DMP6023LE", "Q_COIL", "DMP6023LE-13", 130, 50)
    for p in pin(qc, name="D"):
        s.label(p, "VIN_COIL")
    for p in pin(qc, name="S"):
        s.label(p, "+12V_COIL")
    for p in pin(qc, name="G"):
        s.label(p, "QCOIL_G")
    two_pin(s, "Device:R", "R_COIL_G", "100k", 130, 28, "QCOIL_G", "GND")
    two_pin(s, "windlass:DIODE_OPEN", "D_Z_COIL", "BZT52C12", 165, 50, "+12V_COIL", "QCOIL_G")
    s.flag(170, 65, "+12V_COIL")
    s.flag(20, 20, "GND")
    s.note(
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        "IO3": "IO3_NET",
        "IO4": "TWAI_TX",
        "IO5": "TWAI_RX",
        "IO6": "REED_GPIO",
        "IO7": "UP_SENSE",
        "IO8": "DN_SENSE",
        "IO9": "UP_REQ",
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        "RXD0": "UART_RX",
    }
    connect_named(s, m, gpio)
    two_pin(s, "Device:R", "R10", "10k", 90, 210, "EN_NET", "+3V3")
    two_pin(s, "Device:C", "C10", "1uF", 90, 190, "EN_NET", "GND")
    sw = s.place(
        "Switch:SW_Push",
        "SW_RST",
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        "Button_Switch_SMD:SW_SPST_TL3342",
    )
    connect_named(s, sw, {"1": "EN_NET", "2": "GND"})
    two_pin(s, "Device:R", "R11", "10k", 90, 150, "IO0_NET", "+3V3")
    swb = s.place(
        "Switch:SW_Push",
        "SW_BOOT",
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        "Button_Switch_SMD:SW_SPST_TL3342",
    )
    connect_named(s, swb, {"1": "IO0_NET", "2": "GND"})
    two_pin(s, "Device:R", "R12", "10k", 90, 120, "IO3_NET", "GND")
    two_pin(s, "Device:C", "C11", "10uF", 200, 210, "+3V3", "GND")
    two_pin(s, "Device:C", "C12", "100nF", 220, 210, "+3V3", "GND")
    # Request pins idle low if the GPIO is high-Z. These pulldowns are the default-OFF for the coil requests.
    two_pin(s, "Device:R", "R13", "100k", 230, 160, "UP_REQ", "GND")
    two_pin(s, "Device:R", "R14", "100k", 230, 145, "DN_REQ", "GND")
    for ref, net, x in (
        ("TP_TX", "UART_TX", 40),
        ("TP_RX", "UART_RX", 55),
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    )
    two_pin(s, "Device:R", "R15", "5.1k", 270, 120, "CC1", "GND")
    two_pin(s, "Device:R", "R16", "5.1k", 270, 105, "CC2", "GND")
    two_pin(s, "Device:R", "R17", "22", 250, 130, "USB_DP", "USB_DP_C")
    two_pin(s, "Device:R", "R18", "22", 250, 115, "USB_DN", "USB_DN_C")
    # ST pinout, SOT-23-6: 1 and 6 are I/O1, 3 and 4 are I/O2, 2 is GND, 5 is VBUS.
    # The I/O pins sit on the connector side of the 22 ohm resistors. Pin 5 is USB_VBUS, not +5V.
    esd = s.place("Power_Protection:USBLC6-2SC6", "U_ESD", "USBLC6-2SC6", 280, 155)
    connect_named(
        s,
        esd,
        {"I/O1": "USB_DP_C", "I/O2": "USB_DN_C", "GND": "GND", "VBUS": "USB_VBUS"},
    )
    two_pin(s, "Device:R", "R19", "1M", 320, 100, "USB_SHIELD", "GND")
    two_pin(s, "Device:C", "C13", "100nF", 340, 100, "USB_SHIELD", "GND")
    s.note(
        20,
        80,
        "CC 5.1k is USB Type-C Rd for a device port. 22 ohm series resistors are preliminary full-speed series values, not a safety rating.\\n"
        "U_ESD is USBLC6-2SC6, SOT-23-6. Both I/O1 pins are USB_DP_C and both I/O2 pins are USB_DN_C, on the connector side of R17 and R18.\\n"
        "Its VBUS pin is USB_VBUS. That net is not +5V and not +3V3. The device does not source VBUS and does not present Rp.\\n"
        "Shield is 1M || 100nF to board GND, not a hard chassis bond. Chassis bond is OPEN.\\n"
        "10 uF + 100 nF at the module 3V3 pin follows the Espressif guidance to put bulk capacitance at the module power pin.\\n"
        "GPIO1 is WDI_FUTURE. The relay sheet uses it as the heartbeat. This sheet does not toggle it, and the prototype firmware is not modified.",
    )


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        250,
        "REED rev 0.7. Two modes, one isolator, one isolated 3.3 V rail. REED_RET is not GND, UP_RET, DN_RET or GND_CAN.\\n"
        "JP_REED is a 2.54 mm 1x03 header. Copper does not join the pins. SH_REED is the loose shunt, default on pins 1-2.\\n"
        "Pin 2 is REED_ISO. Pin 1 is LOFRANS_NODE. Pin 3 is DRY_A. The 4.7k pull-up is on DRY_A only.\\n"
        "MEJ2S0503SC is 5 V to 3.3 V. A 51 ohm preload is about 65 mA, above 10 percent of the 606 mA rating, so the published load envelope applies.\\n"
        "ISO7721 field supply is 3.3 V on purpose. At 5 V, VIH would be 3.5 V and the measured 3.22 V idle would not be a reliable high.",
    )
    dcdc = s.place("windlass:MEJ2S", "U4", "MEJ2S0503SC", 40, 180)
    connect_named(s, dcdc, {"1": "+5V", "2": "GND", "7": "REED_3V3", "5": "REED_RET"})
    two_pin(s, "Device:C", "C24", "100nF", 40, 150, "+5V", "GND")
    two_pin(s, "Device:C", "C20", "100nF", 80, 150, "REED_3V3", "REED_RET")
    two_pin(s, "Device:R", "R24", "51_0.5W", 100, 150, "REED_3V3", "REED_RET")
    # Lofrans conditioner. 10k series, 47k pull-down, clamps on the switch throw.
    two_pin(s, "Device:R", "R20", "10k", 140, 200, "REED_SIG", "LOFRANS_NODE")
    two_pin(s, "Device:D_Schottky", "D20", "BAT54W", 170, 200, "REED_3V3", "LOFRANS_NODE", "Diode_SMD:D_SOD-123")
    two_pin(s, "Device:D_Schottky", "D21", "BAT54W", 170, 180, "LOFRANS_NODE", "REED_RET", "Diode_SMD:D_SOD-123")
    jp = s.place(
        "Jumper:Jumper_3_Open",
        "JP_REED",
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    shunt = s.place("Connector_Generic:Conn_01x02", "SH_REED", "SHUNT_2.54", 250, 175, on_board="no")
    for p in shunt:
        s.nc(p)
    # Dry contact. Pull-up exists only on DRY_A, which is J_REED pin 3.
    two_pin(s, "Device:R", "R22", "4.7k", 210, 145, "REED_3V3", "DRY_A")
    # One pull-down, on the isolator side, so Lofrans mode is not two resistors in parallel.
    two_pin(s, "Device:R", "R23", "47k", 240, 155, "REED_ISO", "REED_RET")
    two_pin(s, "Device:C", "C22", "1nF", 240, 135, "REED_ISO", "REED_RET")
    iso = s.place("Isolator:ISO7721D", "U5", "ISO7721DR", 290, 175)
    connect_named(
        s,
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        {
            "VCC1": "+3V3",
            "GND1": "GND",
            "OUTA": "REED_GPIO",
            "INB": "GND",
            "VCC2": "REED_3V3",
            "GND2": "REED_RET",
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        "10 uA leakage in 47k is 0.47 V, below VIL. 100k would be 1.0 V and can cross VIL, so the load cannot be reduced further on this leakage spec.\\n"
        "1 nF at the isolator input with the 10k series resistor is about 10 us, still far under the 30 ms debounce, and it replaces the noise margin the lighter DC load gives up.\\n"
        "ISO7721 (no F suffix) defaults high if the field supply is off. High is idle. The existing firmware counts a rising edge, not a held low.\\n"
        "Lofrans position is one shunt on pins 1-2. DRY_A stays open, so the pull-up cannot reach REED_ISO, LOFRANS_NODE or REED_SIG.\\n"
        "Dry position is the same shunt on pins 2-3. LOFRANS_NODE stays open, so the pull-up reaches the isolator and does not reach REED_SIG.\\n"
        "Default assembly is pins 1-2. Fit one shunt only. Two shunts would short pin 1 to pin 3.\\n"
        "With the shunt removed, R23 holds REED_ISO low. A held level is not a pulse.\\n"
        "ISO7721 without the F suffix holds its output high when VCC2 is below its UVLO and VCC1 is valid, and the output is high-impedance when VCC1 is below UVLO.\\n"
        "VCC1 is the same +3V3 as the ESP32, so the MCU is not running while the output side is unpowered.\\n"
        "The existing firmware samples the pin at start and does not treat that sample as an edge. It counts a change only after 30 ms, and only when the new level is high and a direction sense input is already active.\\n"
        "Field-supply startup and jumper removal produce a falling edge or no edge. A rising edge from supply shutdown or from inserting the shunt is ignored while the windlass sense is stopped.\\n"
        "R20 and the clamps stay on the Lofrans node in both positions. JP1 only removes the CAN isolator supply. Do not fit both sources at once.\\n"
        "Chain length stays the NVS calibration, default 0.36 m per pulse.",
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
